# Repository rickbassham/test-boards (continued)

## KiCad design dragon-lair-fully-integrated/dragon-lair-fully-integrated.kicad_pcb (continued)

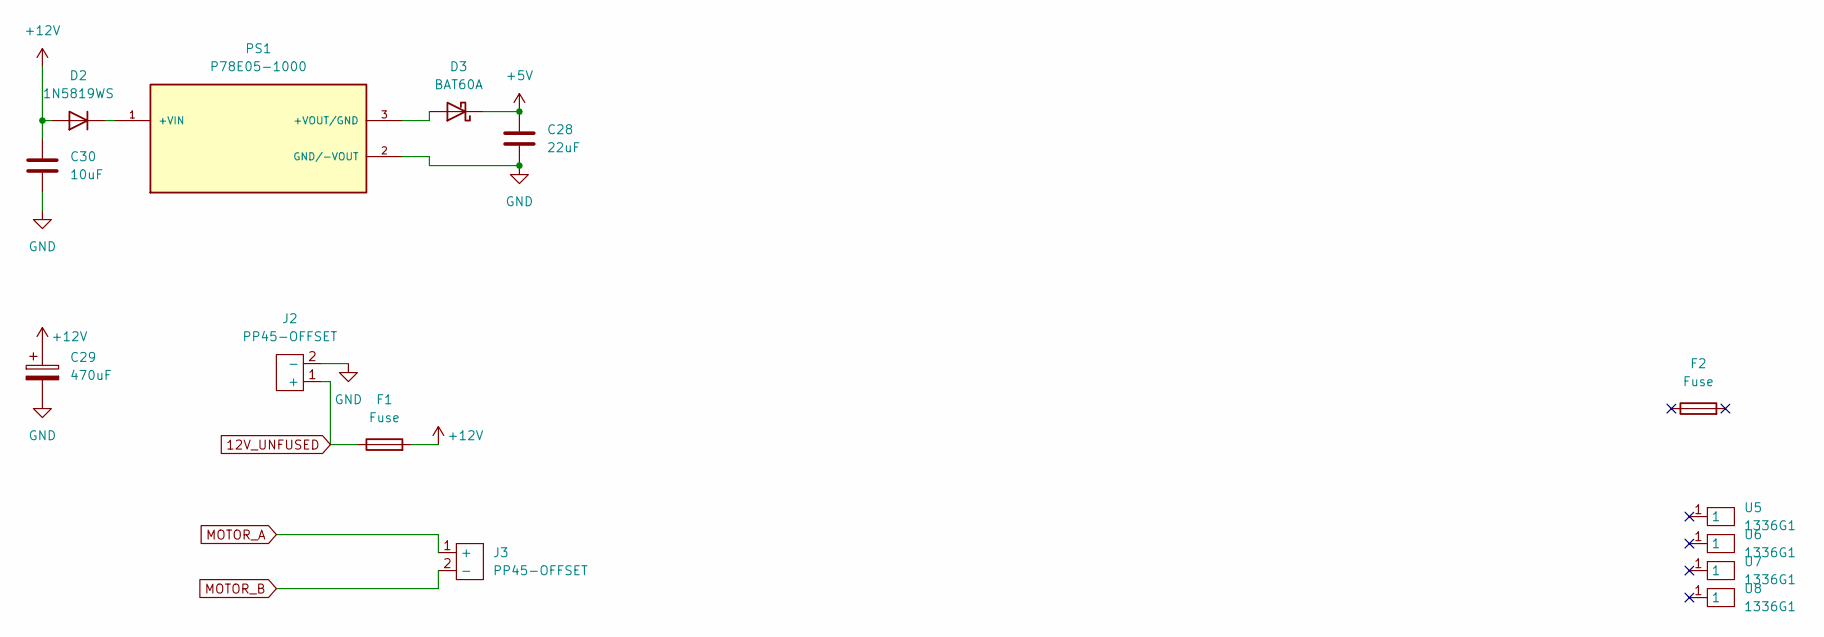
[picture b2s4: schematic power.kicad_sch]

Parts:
C28: 22uF; C_0603_1608Metric; Manufacturer Part FG20X7R1C226MRT06; DigiKey Part 445-173294-1-ND
C29: 470uF; CP_Elec_6.3x7.7; Manufacturer Part 860020474014; DigiKey Part 732-8831-1-ND
C30: 10uF; C_0603_1608Metric; Manufacturer Part FG20X7R1H106KRT06; DigiKey Part 445-173297-1-ND
D2: 1N5819WS; D_SOD-323; LCSC C191023
D3: BAT60A; D_SOD-323; Manufacturer PN BAT60AE6327HTSA1; LCSC C520634
F1: Fuse; Keystone 3522-2 Fuse Holder; Manufacturer Part 3522-2; DigiKey Part 36-3522-2-ND
F2: Fuse; Manufacturer Part 0287030.PXCN; DigiKey Part F4202-ND
J2, J3: PP45-OFFSET; PP45-SHORT; Manufacturer Part 1336G1; DigiKey Part 2243-1336G1-ND
PS1: P78E05-1000; CONV_P78E05-1000; Manufacturer Part P78E05-1000; DigiKey Part 102-5018-ND
U5, U6, U7, U8: 1336G1; Manufacturer Part 1336G1; DigiKey Part 2243-1336G1-ND

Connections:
12V_UNFUSED: F1.1, J2.1 (+)
+5V: C28.1, D3.1 (K); also elsewhere on the board
+12V: C29.1, C30.1, D2.2 (A), F1.2; also elsewhere on the board
GND: C28.2, C29.2, C30.2, J2.2 (-), PS1.2 (GND/-VOUT); also elsewhere on the board
MOTOR_A: J3.1 (+); also elsewhere on the board
MOTOR_B: J3.2 (-); also elsewhere on the board
unnamed: D2.1 (K), PS1.1 (+VIN)
unnamed: D3.2 (A), PS1.3 (+VOUT/GND)

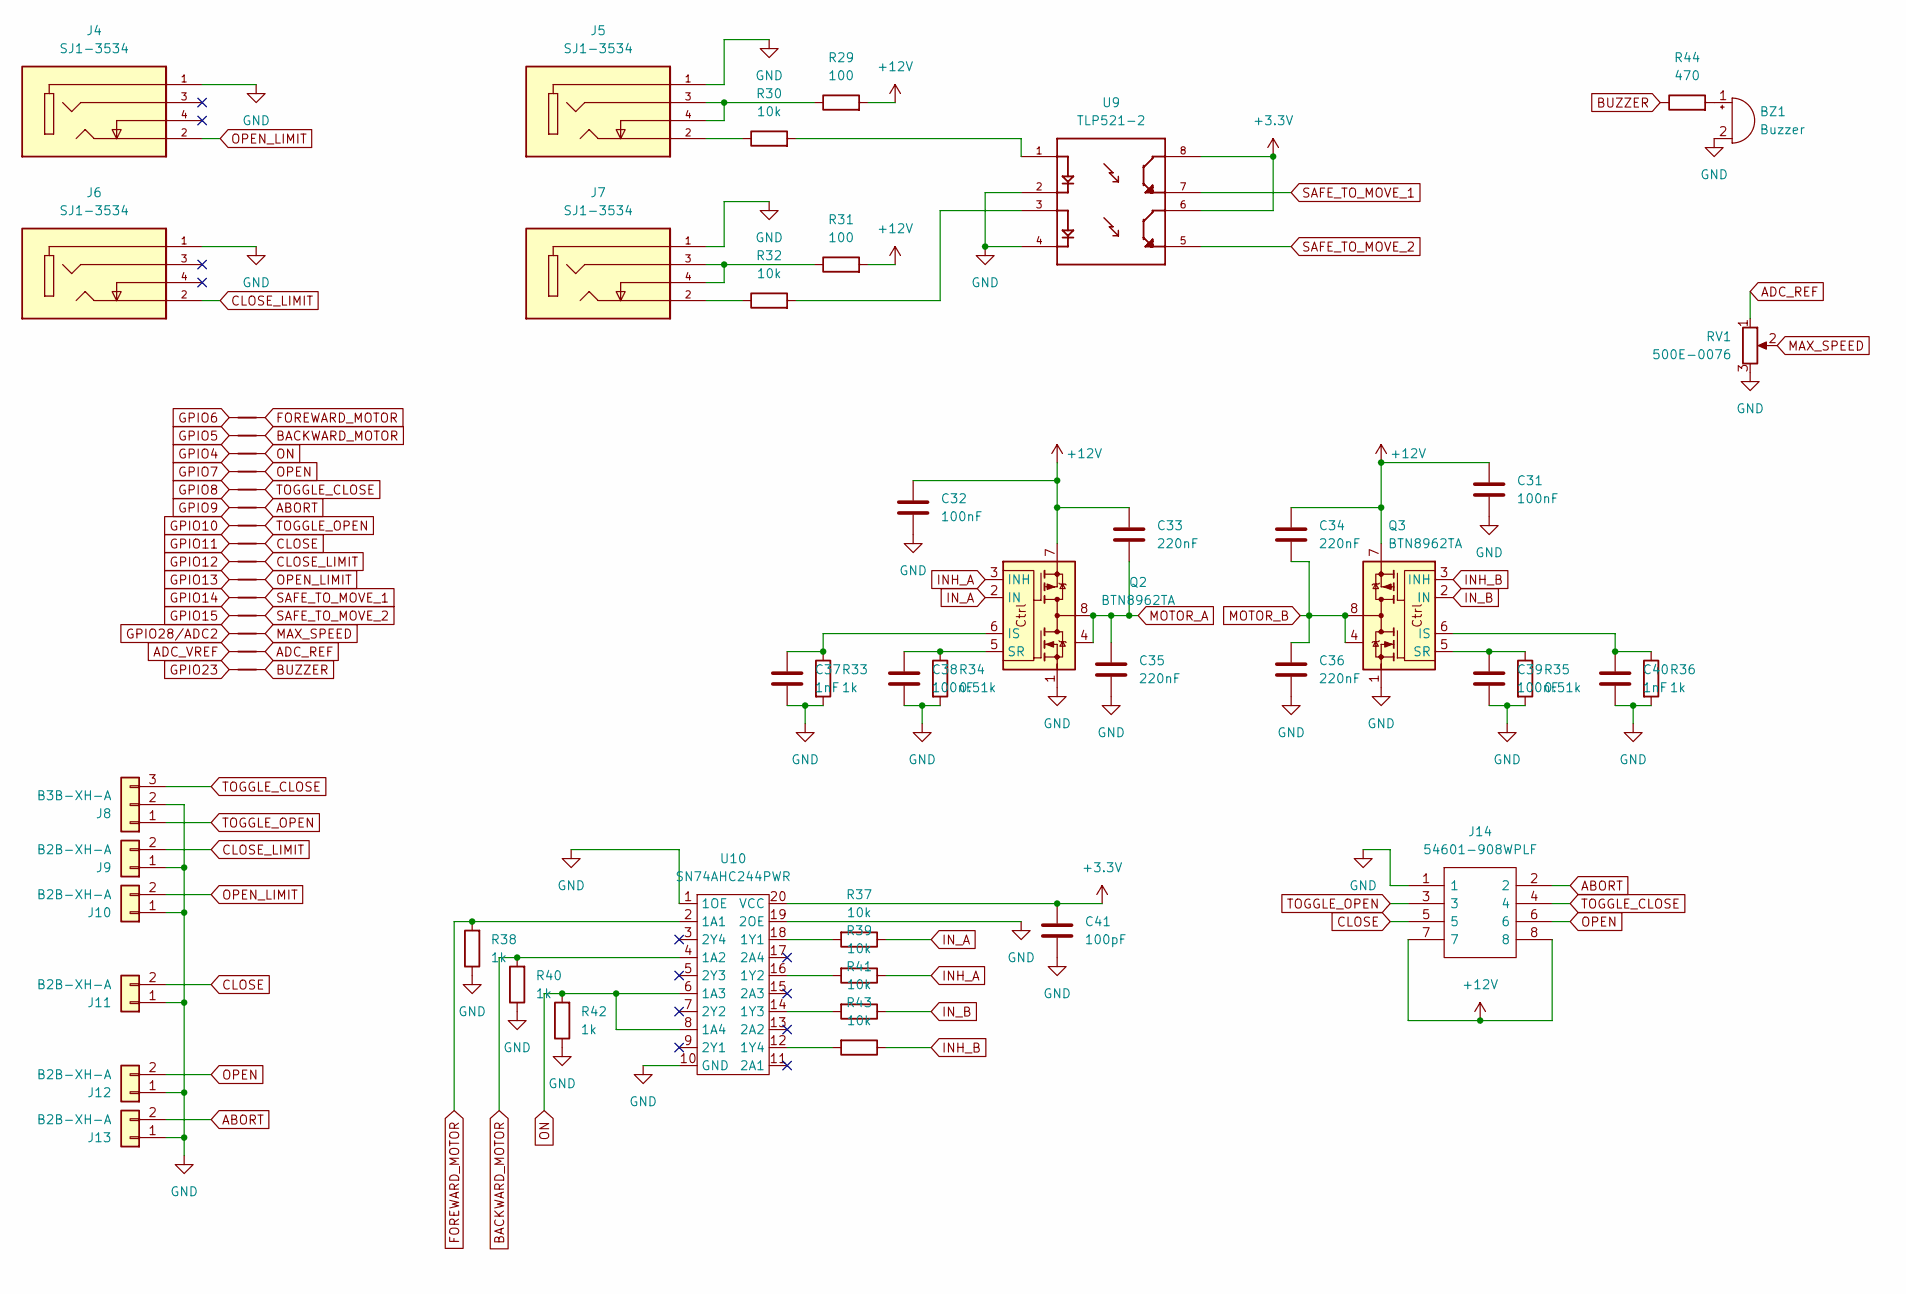
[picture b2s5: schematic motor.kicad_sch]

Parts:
BZ1: Buzzer; AI-3035-TWT-3V-R; Manufacturer Part AI-3035-TWT-3V-R; DigiKey Part 668-1204-ND
C31, C32, C38, C39: 100nF; C_0402_1005Metric; jlc 0603
C33, C34, C35, C36: 220nF; C_0603_1608Metric; jlc 0603
C37, C40: 1nF; C_0402_1005Metric; jlc 0603
C41: 100pF; C_0402_1005Metric; jlc 0603
J4, J5, J6, J7: SJ1-3534; CUI_SJ1-3534; Manufacturer Part SJ1-3534; DigiKey Part CP1-3534-ND
J8: B3B-XH-A; JST_XH_B3B-XH-A_1x03_P2.50mm_Vertical; Manufacturer Part B3B-XH-A(LF)(SN); DigiKey Part 455-2248-ND
J9, J10, J11, J12, J13: B2B-XH-A; JST_XH_B2B-XH-A_1x02_P2.50mm_Vertical; Manufacturer Part B2B-XH-A(LF)(SN); DigiKey Part 455-2247-ND
J14: 54601-908WPLF; 54601908WPLF; Manufacturer Part 54601-908WPLF; DigiKey Part 609-5081-ND
NT1, NT2, NT3, NT4, NT5, NT6, NT7, NT8, NT9, NT10, NT11, NT12, NT13, NT14, NT15: NetTie_2; NetTie-2_SMD_Pad0.5mm
Q2, Q3: BTN8962TA; TO-263-7_TabPin8; jlc TO-263-7
R29, R31: 100; R_0402_1005Metric; Manufacturer Part MBA02040C1000FCT00; LCSC C25076
R30, R32: 10k; R_0402_1005Metric; Manufacturer Part MRS16000C1002FRP00; LCSC C25744
R33, R36, R38, R40, R42: 1k; R_0402_1005Metric; jlc 0603
R34, R35: 0.51k; R_0402_1005Metric; jlc 0603
R37, R39, R41, R43: 10k; R_0402_1005Metric; jlc 0603
R44: 470; R_0402_1005Metric; LCSC C25117
RV1: 500E-0076; 500E−0076; Manufacturer Part 3386P-1-102LF; DigiKey Part 3386P-102LF-ND
U9: TLP521-2; SOP-8_6.62x9.15mm_P2.54mm; Manufacturer Part TLP521-2XGB; DigiKey Part TLP521-2XGB-ND
U10: SN74AHC244PWR; TSSOP-20_4.4x6.5mm_P0.65mm; jlc TSSOP20_44MM_065P

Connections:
+3V3: C41.1, U9.6, U9.8, U10.20 (VCC); also elsewhere on the board
+12V: C31.1, C32.1, C33.1, C34.1, J14.7, J14.8, Q2.7, Q3.7, R29.2, R31.2; also elsewhere on the board
ABORT: J13.2, J14.2, NT6.2
ADC_REF: NT14.2, RV1.1
ADC_VREF: NT14.1; also elsewhere on the board
BACKWARD_MOTOR: NT2.2, R40.2, U10.4 (1A2)
BUZZER: NT15.2, R44.1
CLOSE: J11.2, J14.5, NT8.2
CLOSE_LIMIT: J6.2, J9.2, NT9.2
FOREWARD_MOTOR: NT1.2, R38.2, U10.2 (1A1)
GND: BZ1.2 (+), C31.2, C32.2, C35.2, C36.2, C37.2, C38.2, C39.2, C40.2, C41.2, J4.1, J5.1, J6.1, J7.1, J8.2, J9.1, J10.1, J11.1, J12.1, J13.1, J14.1, Q2.1, Q3.1, R33.2, R34.2, R35.2, R36.2, R38.1, R40.1, R42.1, RV1.3, U9.2, U9.4, U10.1 (1OE), U10.10 (GND), U10.19 (2OE); also elsewhere on the board
GPIO4: NT3.1; also elsewhere on the board
GPIO5: NT2.1; also elsewhere on the board
GPIO6: NT1.1; also elsewhere on the board
GPIO7: NT4.1; also elsewhere on the board
GPIO8: NT5.1; also elsewhere on the board
GPIO9: NT6.1; also elsewhere on the board
GPIO10: NT7.1; also elsewhere on the board
GPIO11: NT8.1; also elsewhere on the board
GPIO12: NT9.1; also elsewhere on the board
GPIO13: NT10.1; also elsewhere on the board
GPIO14: NT11.1; also elsewhere on the board
GPIO15: NT12.1; also elsewhere on the board
GPIO23: NT15.1; also elsewhere on the board
GPIO28/ADC2: NT13.1; also elsewhere on the board
INH_A: Q2.3 (INH), R39.1
INH_B: Q3.3 (INH), R43.1
IN_A: Q2.2 (IN), R37.1
IN_B: Q3.2 (IN), R41.1
MAX_SPEED: NT13.2, RV1.2
MOTOR_A: C33.2, C35.1, Q2.4, Q2.8; also elsewhere on the board
MOTOR_B: C34.2, C36.1, Q3.4, Q3.8; also elsewhere on the board
unnamed: BZ1.1 (-), R44.2
unnamed: C37.1, Q2.6 (IS), R33.1
unnamed: C38.1, Q2.5 (SR), R34.1
unnamed: C39.1, Q3.5 (SR), R35.1
unnamed: C40.1, Q3.6 (IS), R36.1
unnamed: J5.2, R30.1
unnamed: J5.3, J5.4, R29.1
unnamed: J7.2, R32.1
unnamed: J7.3, J7.4, R31.1
unnamed: R30.2, U9.1
unnamed: R32.2, U9.3
unnamed: R37.2, U10.18 (1Y1)
unnamed: R39.2, U10.16 (1Y2)
unnamed: R41.2, U10.14 (1Y3)
unnamed: R43.2, U10.12 (1Y4)
ON: NT3.2, R42.2, U10.6 (1A3), U10.8 (1A4)
OPEN: J12.2, J14.6, NT4.2
OPEN_LIMIT: J4.2, J10.2, NT10.2
SAFE_TO_MOVE_1: NT11.2, U9.7
SAFE_TO_MOVE_2: NT12.2, U9.5
TOGGLE_CLOSE: J8.3, J14.4, NT5.2
TOGGLE_OPEN: J8.1, J14.3, NT7.2

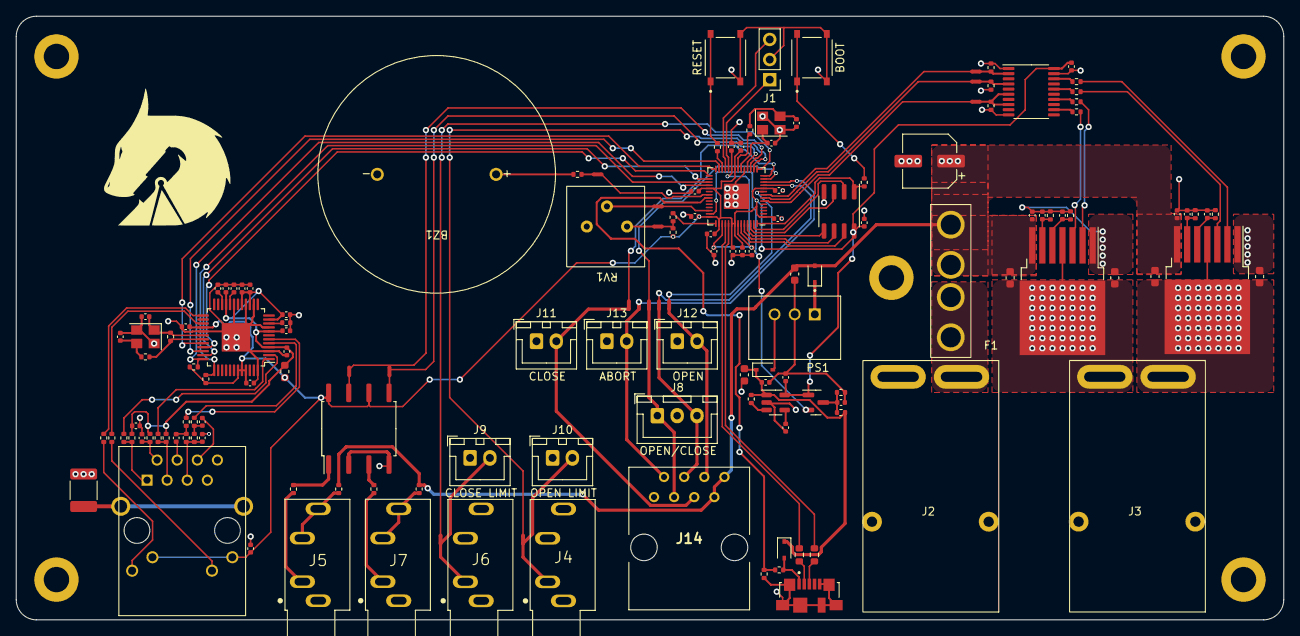
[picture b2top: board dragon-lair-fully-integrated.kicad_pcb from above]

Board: 2 copper layers, 160.0 x 76.2 mm, 152 parts (0 on the bottom side), 114 nets.

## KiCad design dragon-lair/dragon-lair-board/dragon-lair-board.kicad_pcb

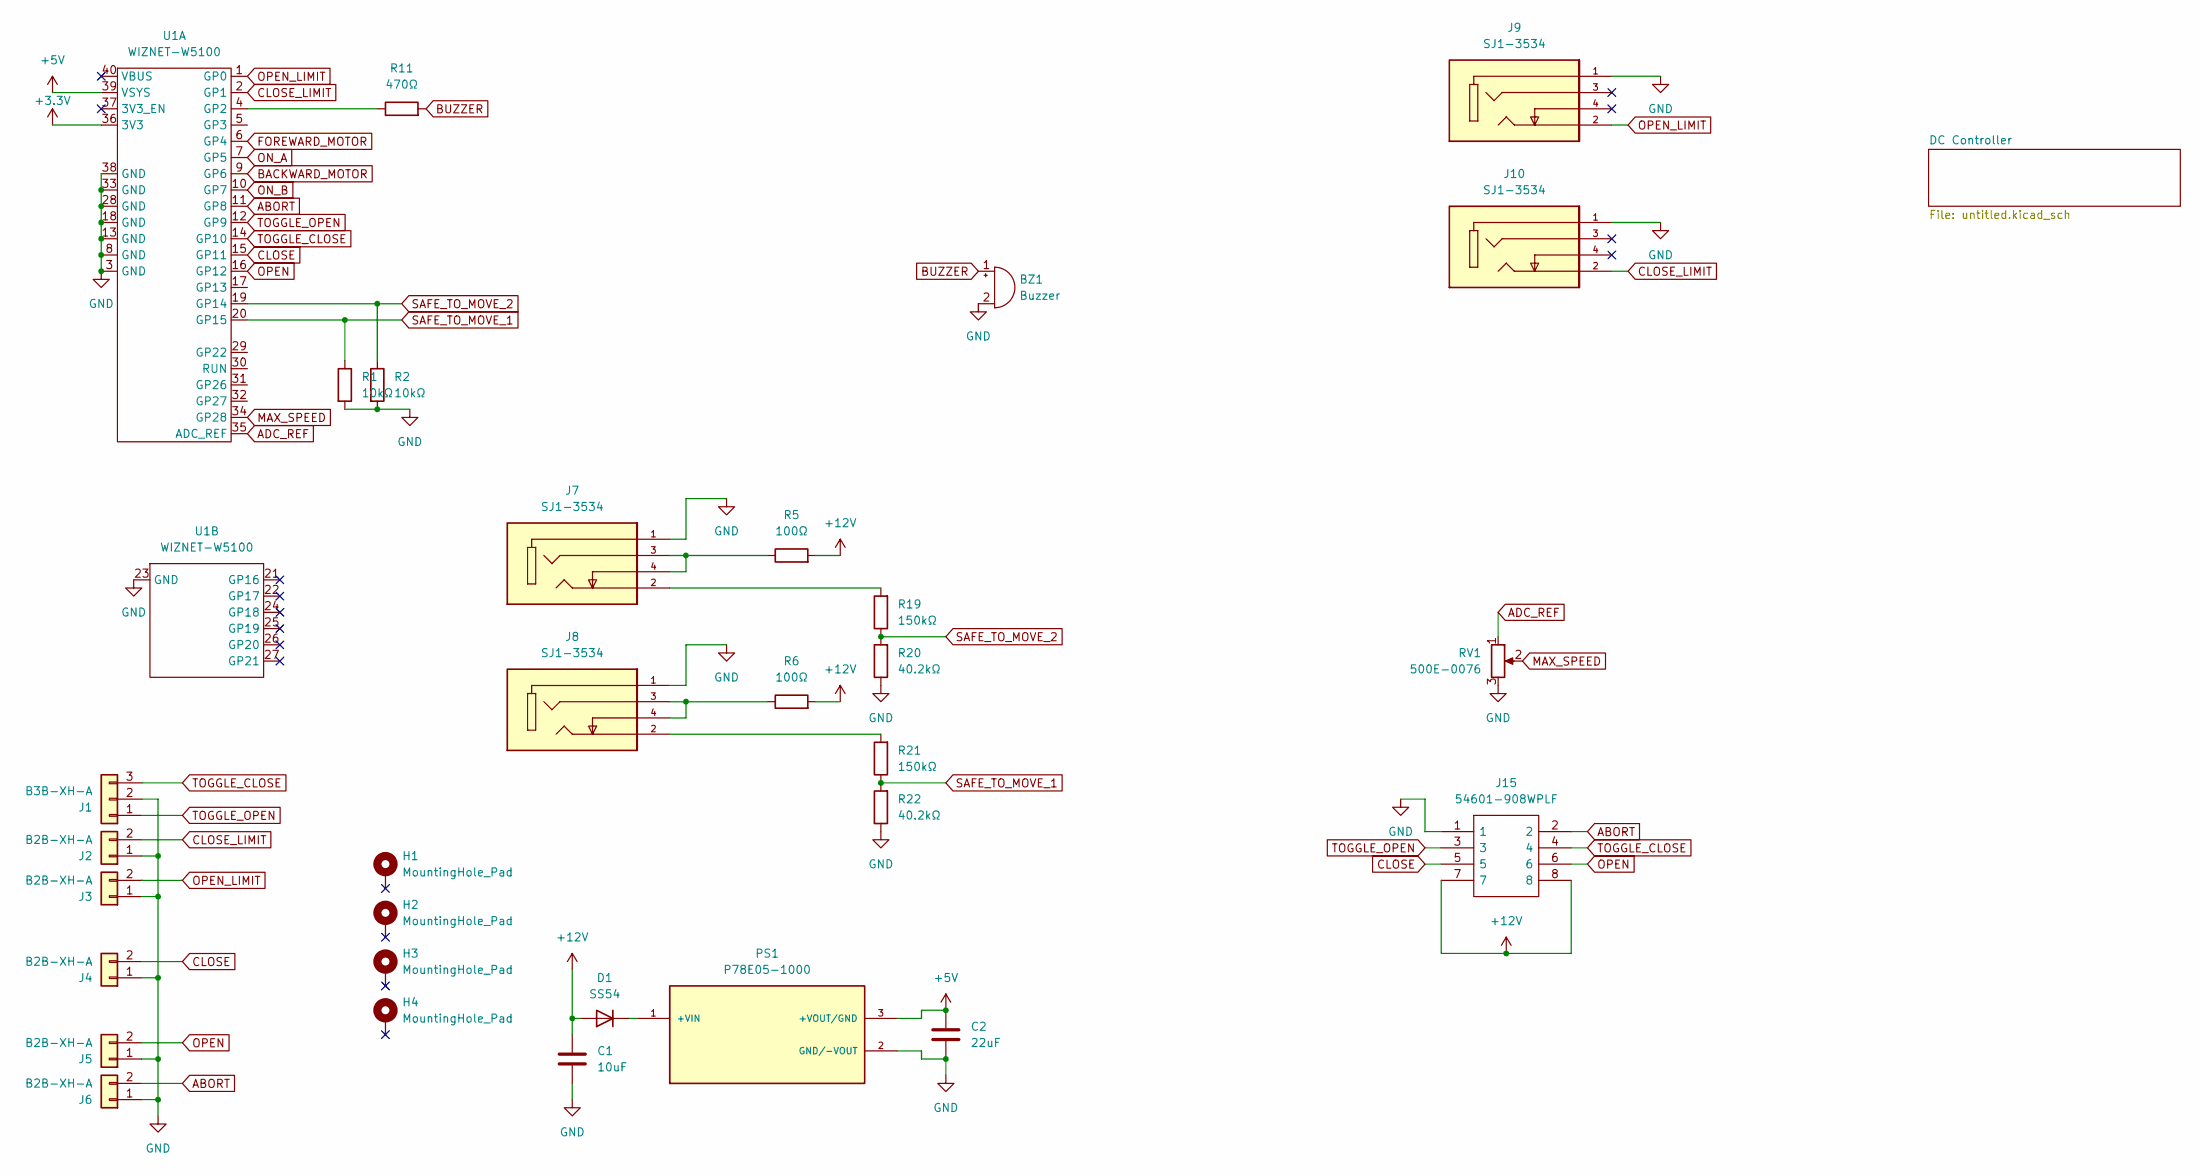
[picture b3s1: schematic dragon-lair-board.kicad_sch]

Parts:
BZ1: Buzzer; AI-3035-TWT-3V-R; Manufacturer Part AI-3035-TWT-3V-R; DigiKey Part 668-1204-ND
C1: 10uF; C_0603_1608Metric; Manufacturer Part FG20X7R1H106KRT06; DigiKey Part 445-173297-1-ND
C2: 22uF; C_0603_1608Metric; Manufacturer Part FG20X7R1C226MRT06; DigiKey Part 445-173294-1-ND
D1: SS54; Manufacturer Part 1N4001GP-E3/54; DigiKey Part 1N4001GP-E3/54GICT-ND
H1, H2, H3, H4: MountingHole_Pad; MountingHole_3.2mm_M3_DIN965_Pad
J1: B3B-XH-A; JST_XH_B3B-XH-A_1x03_P2.50mm_Vertical; Manufacturer Part B3B-XH-A(LF)(SN); DigiKey Part 455-2248-ND
J2, J3, J4, J5, J6: B2B-XH-A; JST_XH_B2B-XH-A_1x02_P2.50mm_Vertical; Manufacturer Part B2B-XH-A(LF)(SN); DigiKey Part 455-2247-ND
J7, J8, J9, J10: SJ1-3534; CUI_SJ1-3534; Manufacturer Part SJ1-3534; DigiKey Part CP1-3534-ND
J15: 54601-908WPLF; 54601908WPLF; Manufacturer Part 54601-908WPLF; DigiKey Part 609-5081-ND
PS1: P78E05-1000; CONV_P78E05-1000; Manufacturer Part P78E05-1000; DigiKey Part 102-5018-ND
R1, R2: 10kΩ; R_0603_1608Metric; Manufacturer Part MRS16000C1002FRP00; DigiKey Part BC3919CT-ND
R5, R6: 100Ω; R_0603_1608Metric; Manufacturer Part MBA02040C1000FCT00; DigiKey Part BC3444CT-ND
R11: 470Ω; R_0603_1608Metric; Manufacturer Part MBA02040C4700FRP00; DigiKey Part BC3516CT-ND
R19, R21: 150kΩ; R_0603_1608Metric; LCSC C114660
R20, R22: 40.2kΩ; R_0603_1608Metric; LCSC C137723
RV1: 500E-0076; 500E−0076; Manufacturer Part 3386P-1-102LF; DigiKey Part 3386P-102LF-ND
U1: WIZNET-W5100; w5100s-evb-pico-no-debug

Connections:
+3.3V: U1.36 (3V3); also elsewhere on the board
+5V: C2.1, PS1.3 (+VOUT/GND), U1.39 (VSYS)
+12V: C1.1, D1.2 (A), J15.7, J15.8, R5.2, R6.2; also elsewhere on the board
ABORT: J6.2, J15.2, U1.11 (GP8)
ADC_REF: RV1.1, U1.35 (ADC_REF)
BACKWARD_MOTOR: U1.9 (GP6); also elsewhere on the board
BUZZER: BZ1.1 (-), R11.2
CLOSE: J4.2, J15.5, U1.15 (GP11)
CLOSE_LIMIT: J2.2, J10.2, U1.2 (GP1)
FOREWARD_MOTOR: U1.6 (GP4); also elsewhere on the board
GND: BZ1.2 (+), C1.2, C2.2, J1.2, J2.1, J3.1, J4.1, J5.1, J6.1, J7.1, J8.1, J9.1, J10.1, J15.1, PS1.2 (GND/-VOUT), R1.2, R2.2, R20.1, R22.1, RV1.3, U1.3 (GND), U1.8 (GND), U1.13 (GND), U1.18 (GND), U1.23 (GND), U1.28 (GND), U1.33 (GND), U1.38 (GND); also elsewhere on the board
MAX_SPEED: RV1.2, U1.34 (GP28)
unnamed: D1.1 (K), PS1.1 (+VIN)
unnamed: J7.2, R19.2
unnamed: J7.3, J7.4, R5.1
unnamed: J8.2, R21.2
unnamed: J8.3, J8.4, R6.1
unnamed: R11.1, U1.4 (GP2)
ON_A: U1.7 (GP5); also elsewhere on the board
ON_B: U1.10 (GP7); also elsewhere on the board
OPEN: J5.2, J15.6, U1.16 (GP12)
OPEN_LIMIT: J3.2, J9.2, U1.1 (GP0)
SAFE_TO_MOVE_1: R1.1, R21.1, R22.2, U1.20 (GP15)
SAFE_TO_MOVE_2: R2.1, R19.1, R20.2, U1.19 (GP14)
TOGGLE_CLOSE: J1.3, J15.4, U1.14 (GP10)
TOGGLE_OPEN: J1.1, J15.3, U1.12 (GP9)

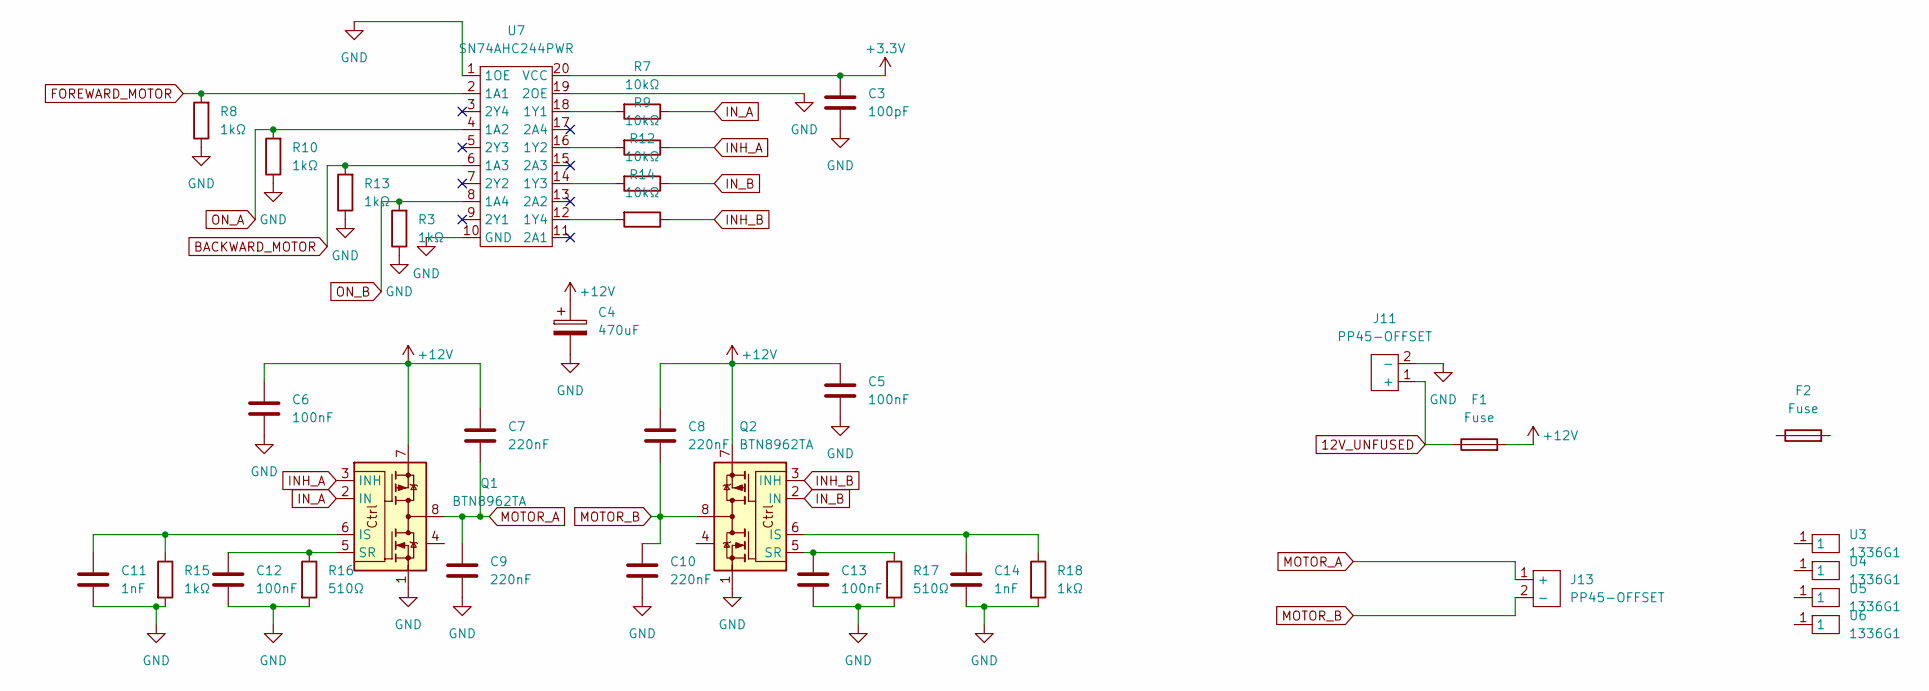
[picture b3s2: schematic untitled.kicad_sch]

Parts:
C3: 100pF; C_0603_1608Metric; jlc 0603
C4: 470uF; CP_Elec_6.3x7.7; Manufacturer Part 860020474014; DigiKey Part 732-8831-1-ND
C5, C6, C12, C13: 100nF; C_0603_1608Metric; jlc 0603
C7, C8, C9, C10: 220nF; C_0603_1608Metric; jlc 0603
C11, C14: 1nF; C_0603_1608Metric; jlc 0603
F1: Fuse; Keystone 3522-2 Fuse Holder; Manufacturer Part 3522-2; DigiKey Part 36-3522-2-ND
F2: Fuse; Manufacturer Part 0287030.PXCN; DigiKey Part F4202-ND
J11, J13: PP45-OFFSET; PP45-SHORT; Manufacturer Part 1336G1; DigiKey Part 2243-1336G1-ND
Q1, Q2: BTN8962TA; TO-263-7_TabPin8; jlc TO-263-7
R3, R8, R10, R13, R15, R18: 1kΩ; R_0603_1608Metric; jlc 0603
R7, R9, R12, R14: 10kΩ; R_0603_1608Metric; jlc 0603
R16, R17: 510Ω; R_0603_1608Metric; jlc 0603
U3, U4, U5, U6: 1336G1; Manufacturer Part 1336G1; DigiKey Part 2243-1336G1-ND
U7: SN74AHC244PWR; TSSOP-20_4.4x6.5mm_P0.65mm; jlc TSSOP20_44MM_065P

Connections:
12V_UNFUSED: F1.1, J11.1 (+)
+3.3V: C3.1, U7.20 (VCC); also elsewhere on the board
+12V: C4.1, C5.1, C6.1, C7.1, C8.1, F1.2, Q1.7, Q2.7; also elsewhere on the board
BACKWARD_MOTOR: R13.2, U7.6 (1A3); also elsewhere on the board
FOREWARD_MOTOR: R8.2, U7.2 (1A1); also elsewhere on the board
GND: C3.2, C4.2, C5.2, C6.2, C9.2, C10.2, C11.2, C12.2, C13.2, C14.2, J11.2 (-), Q1.1, Q2.1, R3.1, R8.1, R10.1, R13.1, R15.2, R16.2, R17.2, R18.2, U7.1 (1OE), U7.10 (GND), U7.19 (2OE); also elsewhere on the board
INH_A: Q1.3 (INH), R9.1
INH_B: Q2.3 (INH), R14.1
IN_A: Q1.2 (IN), R7.1
IN_B: Q2.2 (IN), R12.1
MOTOR_A: C7.2, C9.1, J13.1 (+), Q1.4, Q1.8
MOTOR_B: C8.2, C10.1, J13.2 (-), Q2.4, Q2.8
unnamed: C11.1, Q1.6 (IS), R15.1
unnamed: C12.1, Q1.5 (SR), R16.1
unnamed: C13.1, Q2.5 (SR), R17.1
unnamed: C14.1, Q2.6 (IS), R18.1
unnamed: R7.2, U7.18 (1Y1)
unnamed: R9.2, U7.16 (1Y2)
unnamed: R12.2, U7.14 (1Y3)
unnamed: R14.2, U7.12 (1Y4)
ON_A: R10.2, U7.4 (1A2); also elsewhere on the board
ON_B: R3.2, U7.8 (1A4); also elsewhere on the board

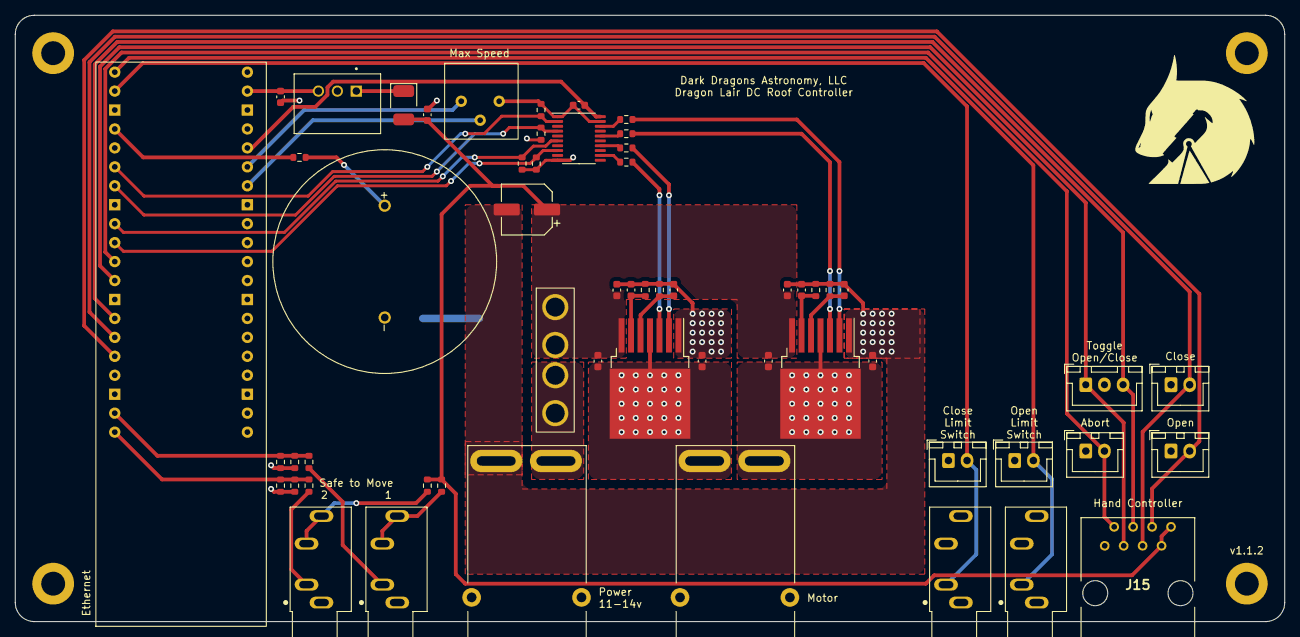
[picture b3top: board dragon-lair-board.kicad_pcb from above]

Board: 2 copper layers, 170.2 x 81.3 mm, 61 parts (0 on the bottom side), 41 nets.

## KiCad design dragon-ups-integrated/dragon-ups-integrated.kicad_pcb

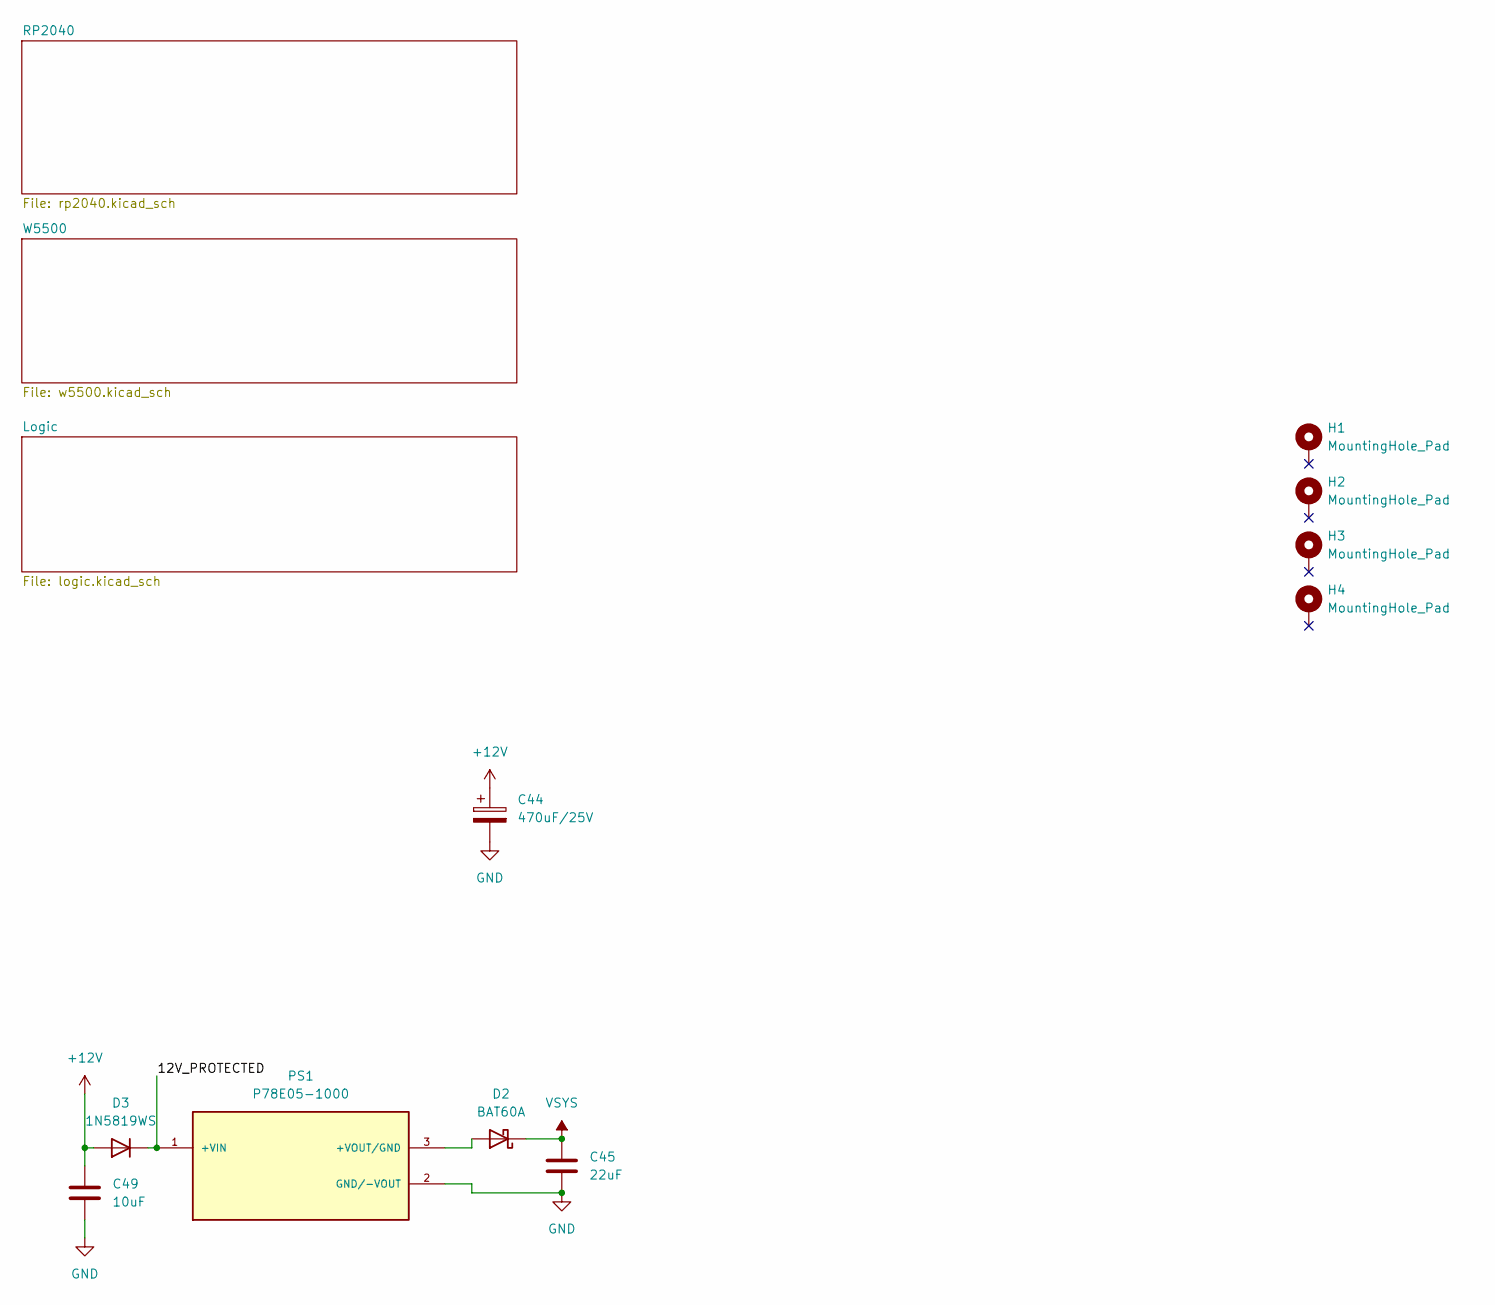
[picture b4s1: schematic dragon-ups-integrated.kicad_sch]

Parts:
C44: 470uF/25V; CP_Elec_10x10.5; LCSC C242138
C45: 22uF; C_0603_1608Metric; Manufacturer Part FG20X7R1C226MRT06; DigiKey Part 445-173294-1-ND
C49: 10uF; C_0603_1608Metric; Manufacturer Part FG20X7R1H106KRT06; DigiKey Part 445-173297-1-ND
D2: BAT60A; D_SOD-323; Manufacturer PN BAT60AE6327HTSA1; LCSC C520634
D3: 1N5819WS; D_SOD-323; LCSC C191023
H1, H2, H3, H4: MountingHole_Pad; MountingHole_3.2mm_M3_DIN965_Pad
PS1: P78E05-1000; CONV_P78E05-1000; Manufacturer Part P78E05-1000; DigiKey Part 102-5018-ND

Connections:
+12V: C44.1, C49.1, D3.2 (A); also elsewhere on the board
/12V_PROTECTED: D3.1 (K), PS1.1 (+VIN)
GND: C44.2, C45.2, C49.2, PS1.2 (GND/-VOUT); also elsewhere on the board
unnamed: D2.2 (A), PS1.3 (+VOUT/GND)
VSYS: C45.1, D2.1 (K); also elsewhere on the board

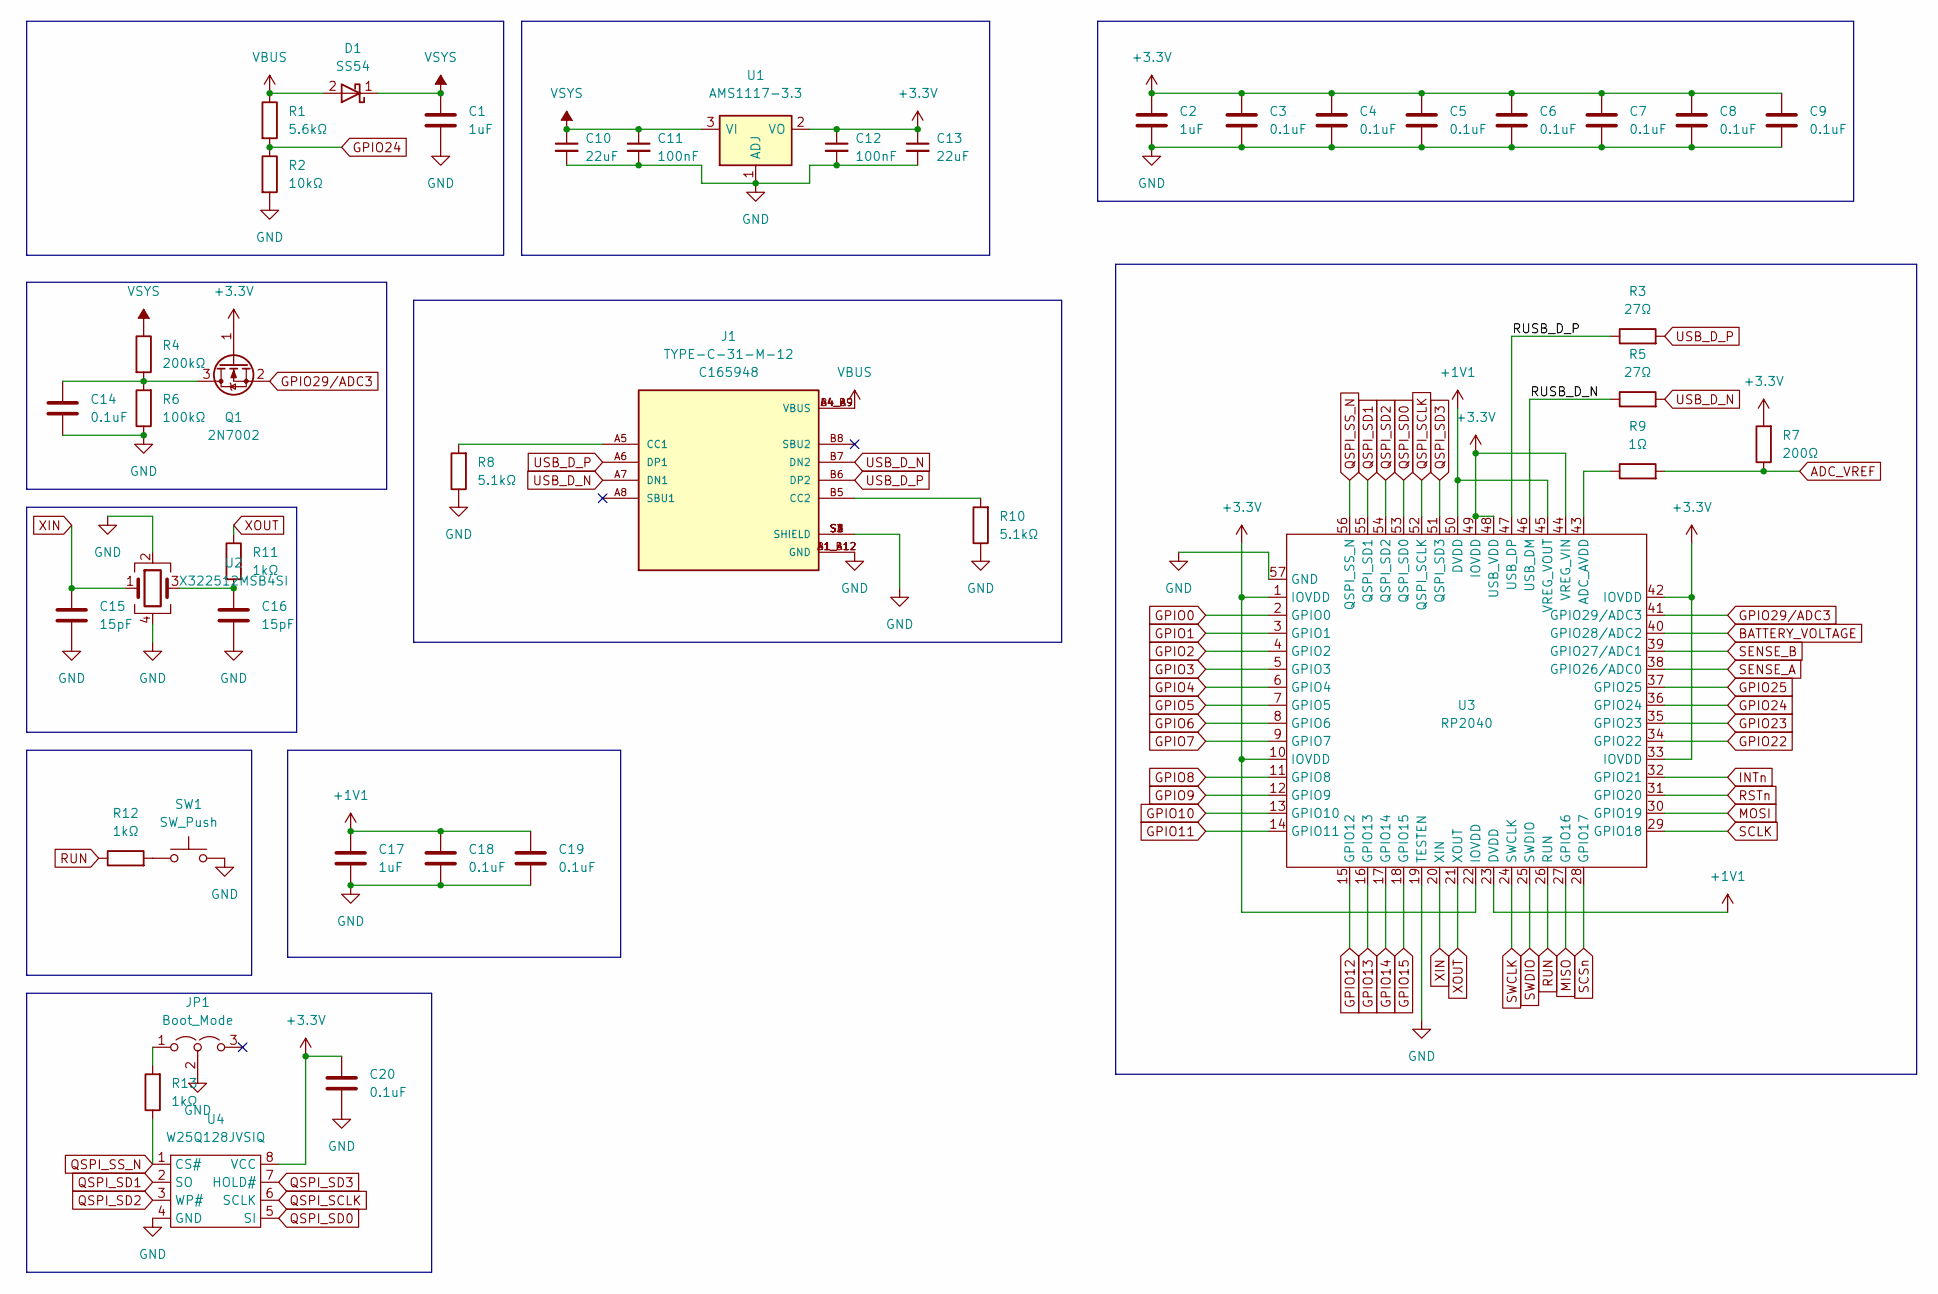
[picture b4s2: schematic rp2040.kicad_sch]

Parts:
C1, C2, C17: 1uF; C_0402_1005Metric; LCSC C52923
C3, C4, C5, C6, C7, C8, C9, C14, C18, C19, C20: 0.1uF; C_0402_1005Metric; LCSC C1525
C10, C13: 22uF; C_0805_2012Metric; LCSC C45783
C11, C12: 100nF; C_0402_1005Metric; LCSC C307331
C15, C16: 15pF; C_0402_1005Metric; LCSC C1548
D1: SS54; D_SMA; LCSC C22452
J1: TYPE-C-31-M-12; HRO_TYPE-C-31-M-12; LCSC C165948
JP1: Boot_Mode; PinHeader_1x03_P2.54mm_Vertical
Q1: 2N7002; SOT-23; LCSC C8545
R1: 5.6kΩ; R_0402_1005Metric; LCSC C25908
R2: 10kΩ; R_0402_1005Metric; LCSC C25744
R3, R5: 27Ω; R_0603_1608Metric; LCSC C25190
R4: 200kΩ; R_0402_1005Metric; LCSC C25764
R6: 100kΩ; R_0402_1005Metric; LCSC C25741
R7: 200Ω; R_0402_1005Metric; LCSC C25087
R8, R10: 5.1kΩ; R_0402_1005Metric
R9: 1Ω; R_0402_1005Metric; LCSC C25086
R11, R12, R13: 1kΩ; R_0402_1005Metric; LCSC C11702
SW1: SW_Push; SW_TS-1187A-B-A-B; LCSC C318884
U1: AMS1117-3.3; SOT-223-3_TabPin2; LCSC C6186
U2: X322512MSB4SI; Crystal_SMD_3225-4Pin_3.2x2.5mm; LCSC C9002
U3: RP2040; LCSC C2040
U4: W25Q128JVSIQ; SOIC-8_3.9x4.9mm_P1.27mm; LCSC C97521

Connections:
+1V1: C17.1, C18.1, C19.1, U3.23 (DVDD), U3.45 (VREG_VOUT), U3.50 (DVDD)
+3V3: C2.1, C3.1, C4.1, C5.1, C6.1, C7.1, C8.1, C9.1, C12.1, C13.1, C20.1, Q1.1 (G), R7.2, U1.2 (VO), U3.1 (IOVDD), U3.10 (IOVDD), U3.22 (IOVDD), U3.33 (IOVDD), U3.42 (IOVDD), U3.44 (VREG_VIN), U3.48 (USB_VDD), U3.49 (IOVDD), U4.8 (VCC); also elsewhere on the board
/RP2040/RUSB_D_N: R5.1, U3.46 (USB_DM)
/RP2040/RUSB_D_P: R3.1, U3.47 (USB_DP)
ADC_VREF: R7.1, R9.2
BATTERY_VOLTAGE: U3.40 (GPIO28/ADC2); also elsewhere on the board
GND: C1.2, C2.2, C3.2, C4.2, C5.2, C6.2, C7.2, C8.2, C9.2, C10.2, C11.2, C12.2, C13.2, C14.2, C15.2, C16.2, C17.2, C18.2, C19.2, C20.2, J1.A1_B12 (GND), J1.B1_A12 (GND), J1.S1 (SHIELD), J1.S2 (SHIELD), J1.S3 (SHIELD), J1.S4 (SHIELD), JP1.2 (C), R2.2, R6.1, R8.1, R10.1, SW1.2, U1.1 (ADJ), U2.2, U2.4, U3.19 (TESTEN), U3.57 (GND), U4.4 (GND); also elsewhere on the board
GPIO0: U3.2 (GPIO0)
GPIO1: U3.3 (GPIO1)
GPIO2: U3.4 (GPIO2)
GPIO3: U3.5 (GPIO3)
GPIO4: U3.6 (GPIO4)
GPIO5: U3.7 (GPIO5)
GPIO6: U3.8 (GPIO6)
GPIO7: U3.9 (GPIO7)
GPIO8: U3.11 (GPIO8)
GPIO9: U3.12 (GPIO9)
GPIO10: U3.13 (GPIO10)
GPIO11: U3.14 (GPIO11)
GPIO12: U3.15 (GPIO12)
GPIO13: U3.16 (GPIO13)
GPIO14: U3.17 (GPIO14)
GPIO15: U3.18 (GPIO15)
GPIO22: U3.34 (GPIO22)
GPIO23: U3.35 (GPIO23)
GPIO24: R1.2, R2.1, U3.36 (GPIO24)
GPIO25: U3.37 (GPIO25)
GPIO29/ADC3: Q1.2 (S), U3.41 (GPIO29/ADC3)
INTn: U3.32 (GPIO21); also elsewhere on the board
MISO: U3.27 (GPIO16); also elsewhere on the board
MOSI: U3.30 (GPIO19); also elsewhere on the board
unnamed: C14.1, Q1.3 (D), R4.2, R6.2
unnamed: C16.1, R11.2, U2.3
unnamed: J1.A5 (CC1), R8.2
unnamed: J1.B5 (CC2), R10.2
unnamed: JP1.1 (A), R13.2
unnamed: R9.1, U3.43 (ADC_AVDD)
unnamed: R12.2, SW1.1
QSPI_SCLK: U3.52 (QSPI_SCLK), U4.6 (SCLK)
QSPI_SD0: U3.53 (QSPI_SD0), U4.5 (SI)
QSPI_SD1: U3.55 (QSPI_SD1), U4.2 (SO)
QSPI_SD2: U3.54 (QSPI_SD2), U4.3 (WP#)
QSPI_SD3: U3.51 (QSPI_SD3), U4.7 (HOLD#)
QSPI_SS_N: R13.1, U3.56 (QSPI_SS_N), U4.1 (CS#)
RSTn: U3.31 (GPIO20); also elsewhere on the board
RUN: R12.1, U3.26 (RUN)
SCLK: U3.29 (GPIO18); also elsewhere on the board
SCSn: U3.28 (GPIO17); also elsewhere on the board
SENSE_A: U3.38 (GPIO26/ADC0); also elsewhere on the board
SENSE_B: U3.39 (GPIO27/ADC1); also elsewhere on the board
SWCLK: U3.24 (SWCLK)
SWDIO: U3.25 (SWDIO)
USB_D_N: J1.A7 (DN1), J1.B7 (DN2), R5.2
USB_D_P: J1.A6 (DP1), J1.B6 (DP2), R3.2
VBUS: D1.2 (A), J1.A4_B9 (VBUS), J1.B4_A9 (VBUS), R1.1
VSYS: C1.1, C10.1, C11.1, D1.1 (K), R4.1, U1.3 (VI); also elsewhere on the board
XIN: C15.1, U2.1, U3.20 (XIN)
XOUT: R11.1, U3.21 (XOUT)
